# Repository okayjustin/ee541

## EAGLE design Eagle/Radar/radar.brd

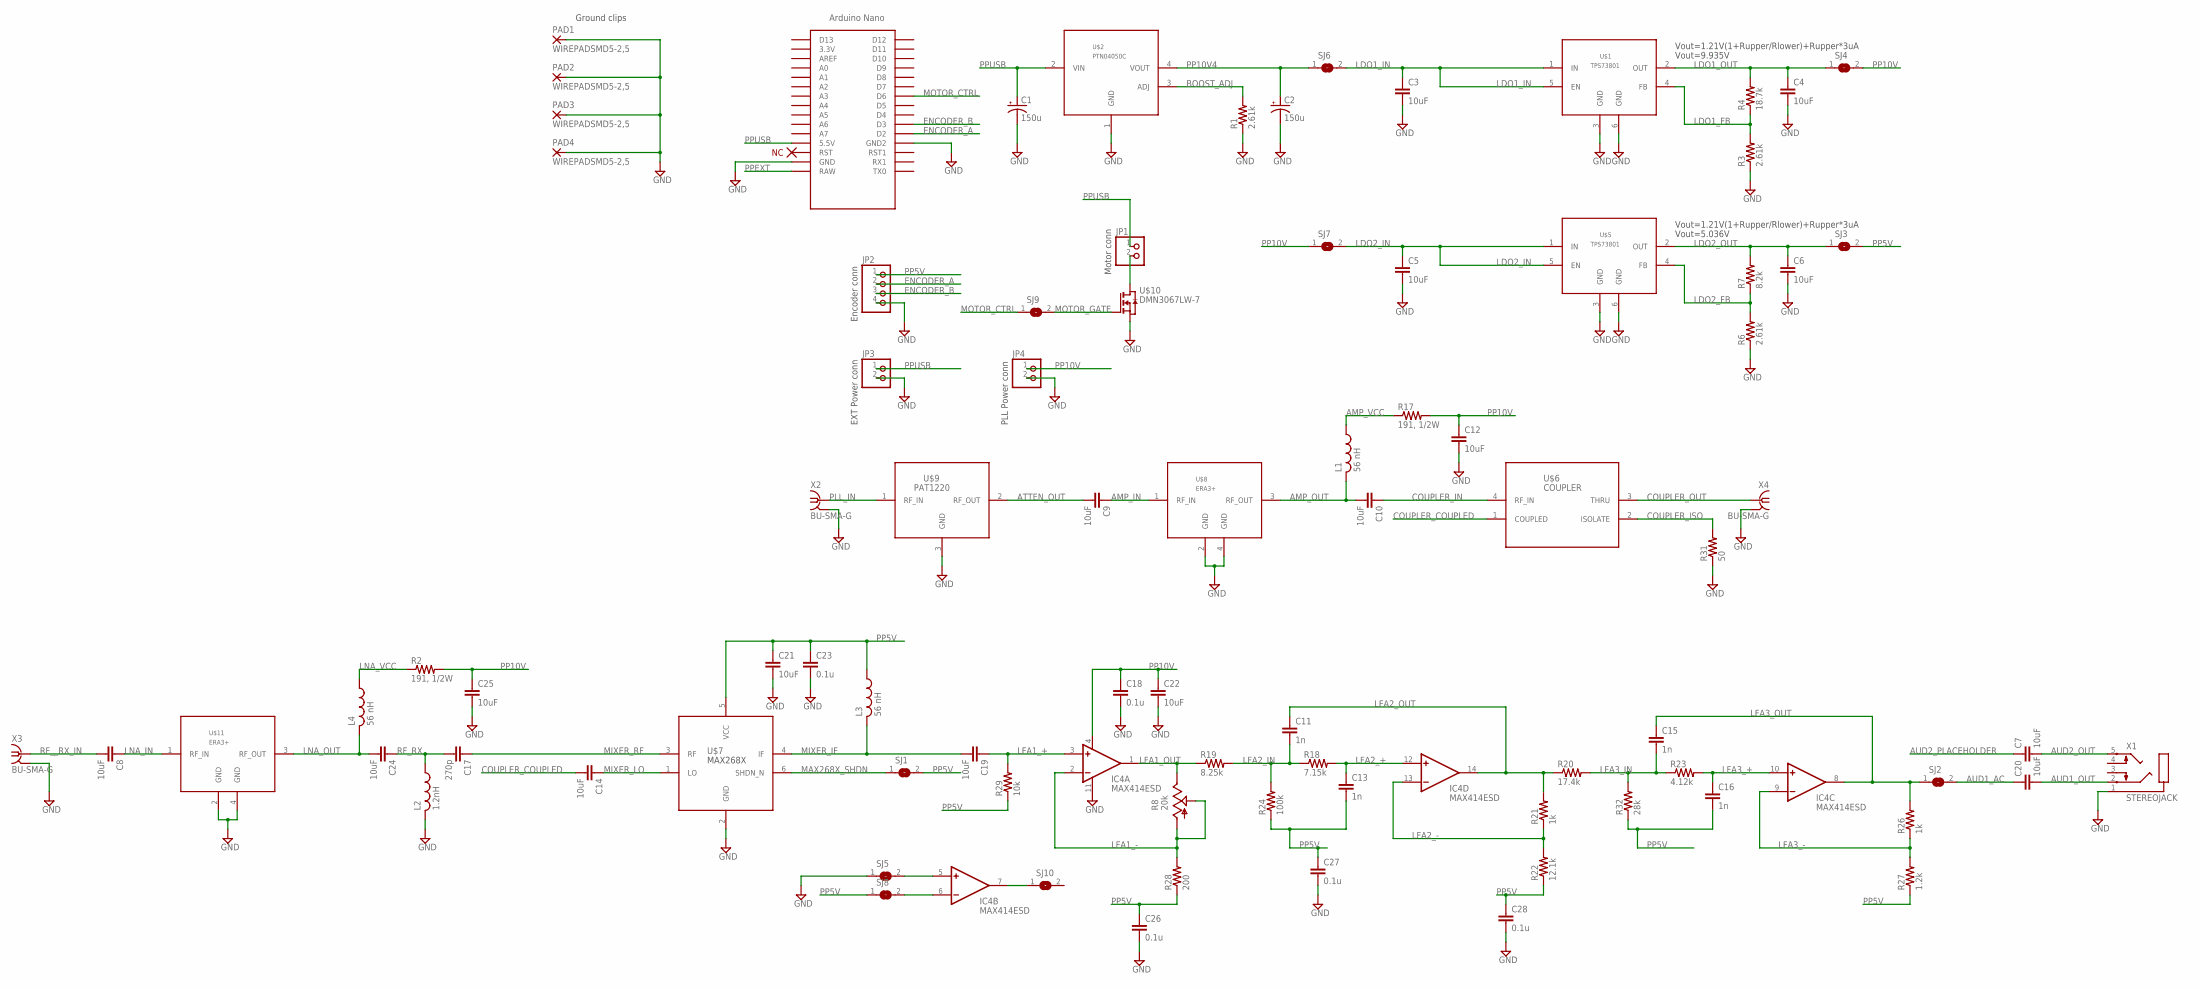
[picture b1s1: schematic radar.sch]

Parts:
C1, C2: 150u; 153CLV-0605; DIGI PCE4443CT-ND
C3, C4, C5, C6, C7, C8, C9, C10, C12, C14, C19, C20, C21, C22, C24, C25: 10uF; C0805K; DIGI 587-2985-1-ND
C11, C13, C15, C16: 1n; C0603; DIGI 311-1085-1-ND
C17: 270p; C0603K; DIGI 399-9054-1-ND
C18, C23, C26, C27, C28: 0.1u; C0603; DIGI 311-1088-1-ND
IC4: MAX414ESD; SO14; DIGI MAX414ESD+-ND
JP1, JP3, JP4: PINHD-1X2; 1X02
JP2: PINHD-1X4; 1X04
L1, L3, L4: 56 nH; 0603; DIGI 712-1443-1-ND
L2: 1.2nH; 0603; DIGI 535-11530-1-ND
PAD1, PAD2, PAD3, PAD4: WIREPADSMD5-2,5; 5-2,5
R1, R3, R6: 2.61k; R0603; DIGI 311-2520-1-ND
R2, R17: 191, 1/2W; R1210; DIGI P191AACT-ND
R4: 18.7k; R0603; DIGI 311-18.7KHRCT-ND
R7: 8.2k; R0603; DIGI 311-2680-1-ND
R8: 20k; B25P; DIGI 3362P-203LF-ND
R18: 7.15k; R0603; DIGI 311-7.15KHRCT-ND
R19: 8.25k; R0603; DIGI RNCP0805FTD8K25CT-ND
R20: 17.4k; R0603; DIGI 311-17.4KHRCT-ND
R21, R26: 1k; R0603; DIGI 311-1.00KHRCT-ND
R22: 12.1k; R0603; DIGI 541-12.1KSCT-ND
R23: 4.12k; R0603; DIGI 311-4.12KHRCT-ND
R24: 100k; R0603; DIGI 541-3247-1-ND
R27: 1.2k; R0603; DIGI 311-1.20KHRCT-ND
R28: 200; R0603; DIGI RNCP0805FTD200RCT-ND
R29: 10k; R0603; DIGI 311-10.0KHRCT-ND
R31: 50; R0603; DIGI RNCP0805FTD49R9CT-ND
R32: 28k; R0603; DIGI 311-28.0KHRCT-ND
SJ1, SJ2, SJ3, SJ4, SJ5, SJ6, SJ7, SJ8, SJ9, SJ10: SJ
U$1, U$5: TPS73801; SOT223-6
U$2: PTN04050C; DIGI 296-20498-ND
U$3: NANO
U$6: COUPLER
U$7: MAX268X; SOT23-6; DIGI MAX2682EUT+TCT-ND
U$8, U$11: ERA3+
U$9: PAT1220; DIGI PAT123CT-ND
U$10: DMN3067LW-7; SOT323; DIGI DMN3067LW-7DICT-ND
X1: STEREOJACK; STX3100; DIGI CP1-3555NG-ND
X2, X3, X4: BU-SMA-G; DIGI ACX2074-ND

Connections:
AMP_IN: C9.1, U$8.1 (RF_IN)
AMP_OUT: C10.2, L1.2, U$8.3 (RF_OUT)
AMP_VCC: L1.1, R17.1
ATTEN_OUT: C9.2, U$9.2 (RF_OUT)
AUD1_AC: C20.1, SJ2.2
AUD1_OUT: C20.2, X1.2
AUD2_OUT: C7.2, X1.5
AUD2_PLACEHOLDER: C7.1
BOOST_ADJ: R1.2, U$2.3 (ADJ)
COUPLER_COUPLED: C14.2, U$6.1 (COUPLED)
COUPLER_IN: C10.1, U$6.4 (RF_IN)
COUPLER_ISO: R31.2, U$6.2 (ISOLATE)
COUPLER_OUT: U$6.3 (THRU), X4.1
ENCODER_A: JP2.2, U$3.D2
ENCODER_B: JP2.3, U$3.D3
GND: C1.-, C2.-, C3.2, C4.2, C5.2, C6.2, C12.2, C18.2, C21.2, C22.2, C23.2, C25.2, C26.2, C27.2, C28.2, IC4.11 (V-), JP2.4, JP3.2, JP4.2, L2.2, PAD1.1, PAD2.1, PAD3.1, PAD4.1, R1.1, R3.1, R6.1, R31.1, SJ5.1, U$1.3 (GND), U$1.6 (GND), U$2.1 (GND), U$3.GND, U$3.GND1 (GND2), U$5.3 (GND), U$5.6 (GND), U$7.2 (GND), U$8.2 (GND), U$8.4 (GND), U$9.3 (GND), U$10.2 (S), U$11.2 (GND), U$11.4 (GND), X1.1, X2.2, X2.3 (2), X2.4 (2), X2.5 (2), X3.2, X3.3 (2), X3.4 (2), X3.5 (2), X4.2, X4.3 (2), X4.4 (2), X4.5 (2)
LDO1_FB: R3.2, R4.1, U$1.4 (FB)
LDO1_IN: C3.1, SJ6.2, U$1.1 (IN), U$1.5 (EN)
LDO1_OUT: C4.1, R4.2, SJ4.1, U$1.2 (OUT)
LDO2_FB: R6.2, R7.1, U$5.4 (FB)
LDO2_IN: C5.1, SJ7.2, U$5.1 (IN), U$5.5 (EN)
LDO2_OUT: C6.1, R7.2, SJ3.1, U$5.2 (OUT)
LFA1_+: C19.1, IC4.3 (+IN), R29.2
LFA1_-: IC4.2 (-IN), R8.A, R8.S, R28.2
LFA1_OUT: IC4.1 (OUT), R8.E, R19.1
LFA2_+: C13.1, IC4.12 (+IN), R18.2
LFA2_-: IC4.13 (-IN), R21.1, R22.2
LFA2_IN: C11.2, R18.1, R19.2, R24.2
LFA2_OUT: C11.1, IC4.14 (OUT), R20.1, R21.2
LFA3_+: C16.1, IC4.10 (+IN), R23.2
LFA3_-: IC4.9 (-IN), R26.1, R27.2
LFA3_IN: C15.2, R20.2, R23.1, R32.2
LFA3_OUT: C15.1, IC4.8 (OUT), R26.2, SJ2.1
LNA_IN: C8.1, U$11.1 (RF_IN)
LNA_OUT: C24.2, L4.2, U$11.3 (RF_OUT)
LNA_VCC: L4.1, R2.1
MAX268X_SHDN: SJ1.1, U$7.6 (SHDN_N)
MIXER_IF: C19.2, L3.2, U$7.4 (IF)
MIXER_LO: C14.1, U$7.1 (LO)
MIXER_RF: C17.1, U$7.3 (RF)
MOTOR_CTRL: SJ9.1, U$3.D6
MOTOR_GATE: SJ9.2, U$10.1 (G)
unnamed: JP1.2, U$10.3 (D)
unnamed: IC4.7 (OUT), SJ10.1
unnamed: IC4.5 (+IN), SJ5.2
unnamed: IC4.6 (-IN), SJ8.2
PLL_IN: U$9.1 (RF_IN), X2.1
PP5V: C13.2, C16.2, C21.1, C23.1, C26.1, C27.1, C28.1, JP2.1, L3.1, R22.1, R24.1, R27.1, R28.1, R29.1, R32.1, SJ1.2, SJ3.2, SJ8.1, U$7.5 (VCC)
PP10V: C12.1, C18.1, C22.1, C25.1, IC4.4 (V+), JP4.1, R2.2, R17.2, SJ4.2, SJ7.1
PP10V4: C2.+, SJ6.1, U$2.4 (VOUT)
PPEXT: U$3.RAW
PPUSB: C1.+, JP1.1, JP3.1, U$2.2 (VIN), U$3.5V (5.5V)
RF_RX: C17.2, C24.1, L2.1
RF__RX_IN: C8.2, X3.1

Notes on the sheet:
Vout=1.21V(1+Rupper/Rlower)+Rupper*3uA
Vout=9.935V
Vout=5.036V
Ground clips
Encoder conn
Motor conn
EXT Power conn
PLL Power conn

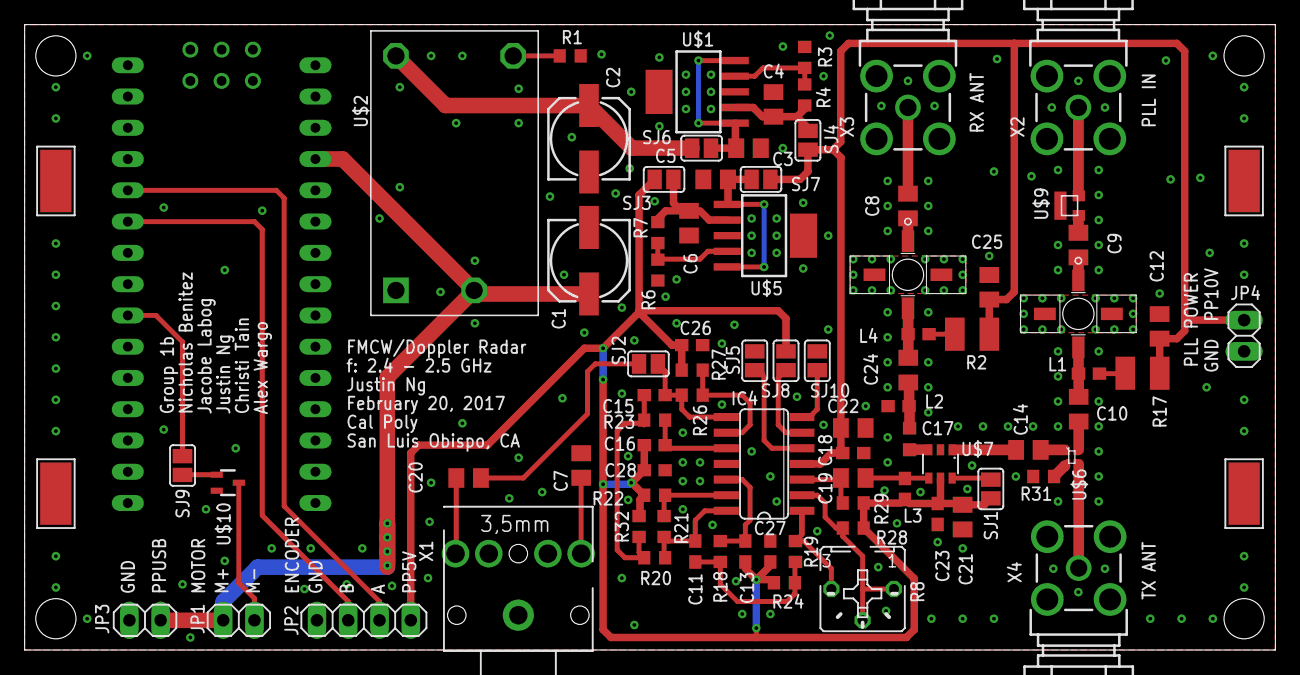
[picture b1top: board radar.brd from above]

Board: 2 copper layers, 101.6 x 50.8 mm, 86 parts (0 on the bottom side), 52 nets.

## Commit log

2017-01-24 Added gitignore
2017-01-24 Removed data folder
2017-01-24 Fixed gitignore
2017-01-24 Updated some print() functions for python3 compatibility. Removed some log10 functions temporarily
2017-01-24 Added plt.show() to actually display the plot...
2017-01-24 Added back the log functions. Appears to work properly now.
2017-01-24 Added plt.show() to cantenna_RTI.py
2017-02-07 Moved software into folder
2017-02-16 Finished power section schematic. Started board
2017-02-16 Added amplifier circuits, ground clips, 3.5mm
2017-02-17 Updated schematic
2017-02-17 Updated digi values
2017-02-18 Finalized sch
2017-02-18 Moved some board parts
2017-02-19 Nearly completed placements on board
2017-02-19 Finished RF routing
2017-02-20 Routing complete
2017-02-20 Routes complete, no drc errors, no erc errors, need silks
2017-02-20 Started silks, gnd stitch complete
2017-02-20 Design complete
2017-02-22 added stuff
2017-02-22 Fixed README
2017-02-22 added more comments for understanding some functions
2017-02-22 Created radar model
2017-02-28 found slightly modified make_sar_image.py in order to create a SAR image file because cantenna_sar.py is not working on python 2.7
2017-02-28 changed datapath for wavFile
2017-02-28 cant get to run on 2.7 yet
2017-02-28 added make_sar_image.py to create SAR images
2017-02-28 Added gear
2017-03-11 Added a bunch of solidworks models
2017-03-11 Nearly completed modeling. Needs switch triggering block
2017-03-11 Design complete. Need to generate illustrator files
2017-03-12 Added illustrator drawings
2017-03-14 Fixed naming for some files
2017-03-17 Added smaller table gear
2017-03-17 base board
2017-03-22 added code
2017-03-22 added stft method to Polar_Image
